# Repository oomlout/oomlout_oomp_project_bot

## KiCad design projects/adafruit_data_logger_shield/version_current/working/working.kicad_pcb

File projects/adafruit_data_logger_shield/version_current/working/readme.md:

# Data-Logger-shield by adafruit  
This is a harvested standardized copy of a project from github.  
The original project can be found at:  
https://github.com/adafruit/Data-Logger-shield  
Please consult that link for additional, details, files, and license information.  
Note: It was auto harvested and if the original repo had more than one board file or anything out of the ordinary the files here are likely not representative.

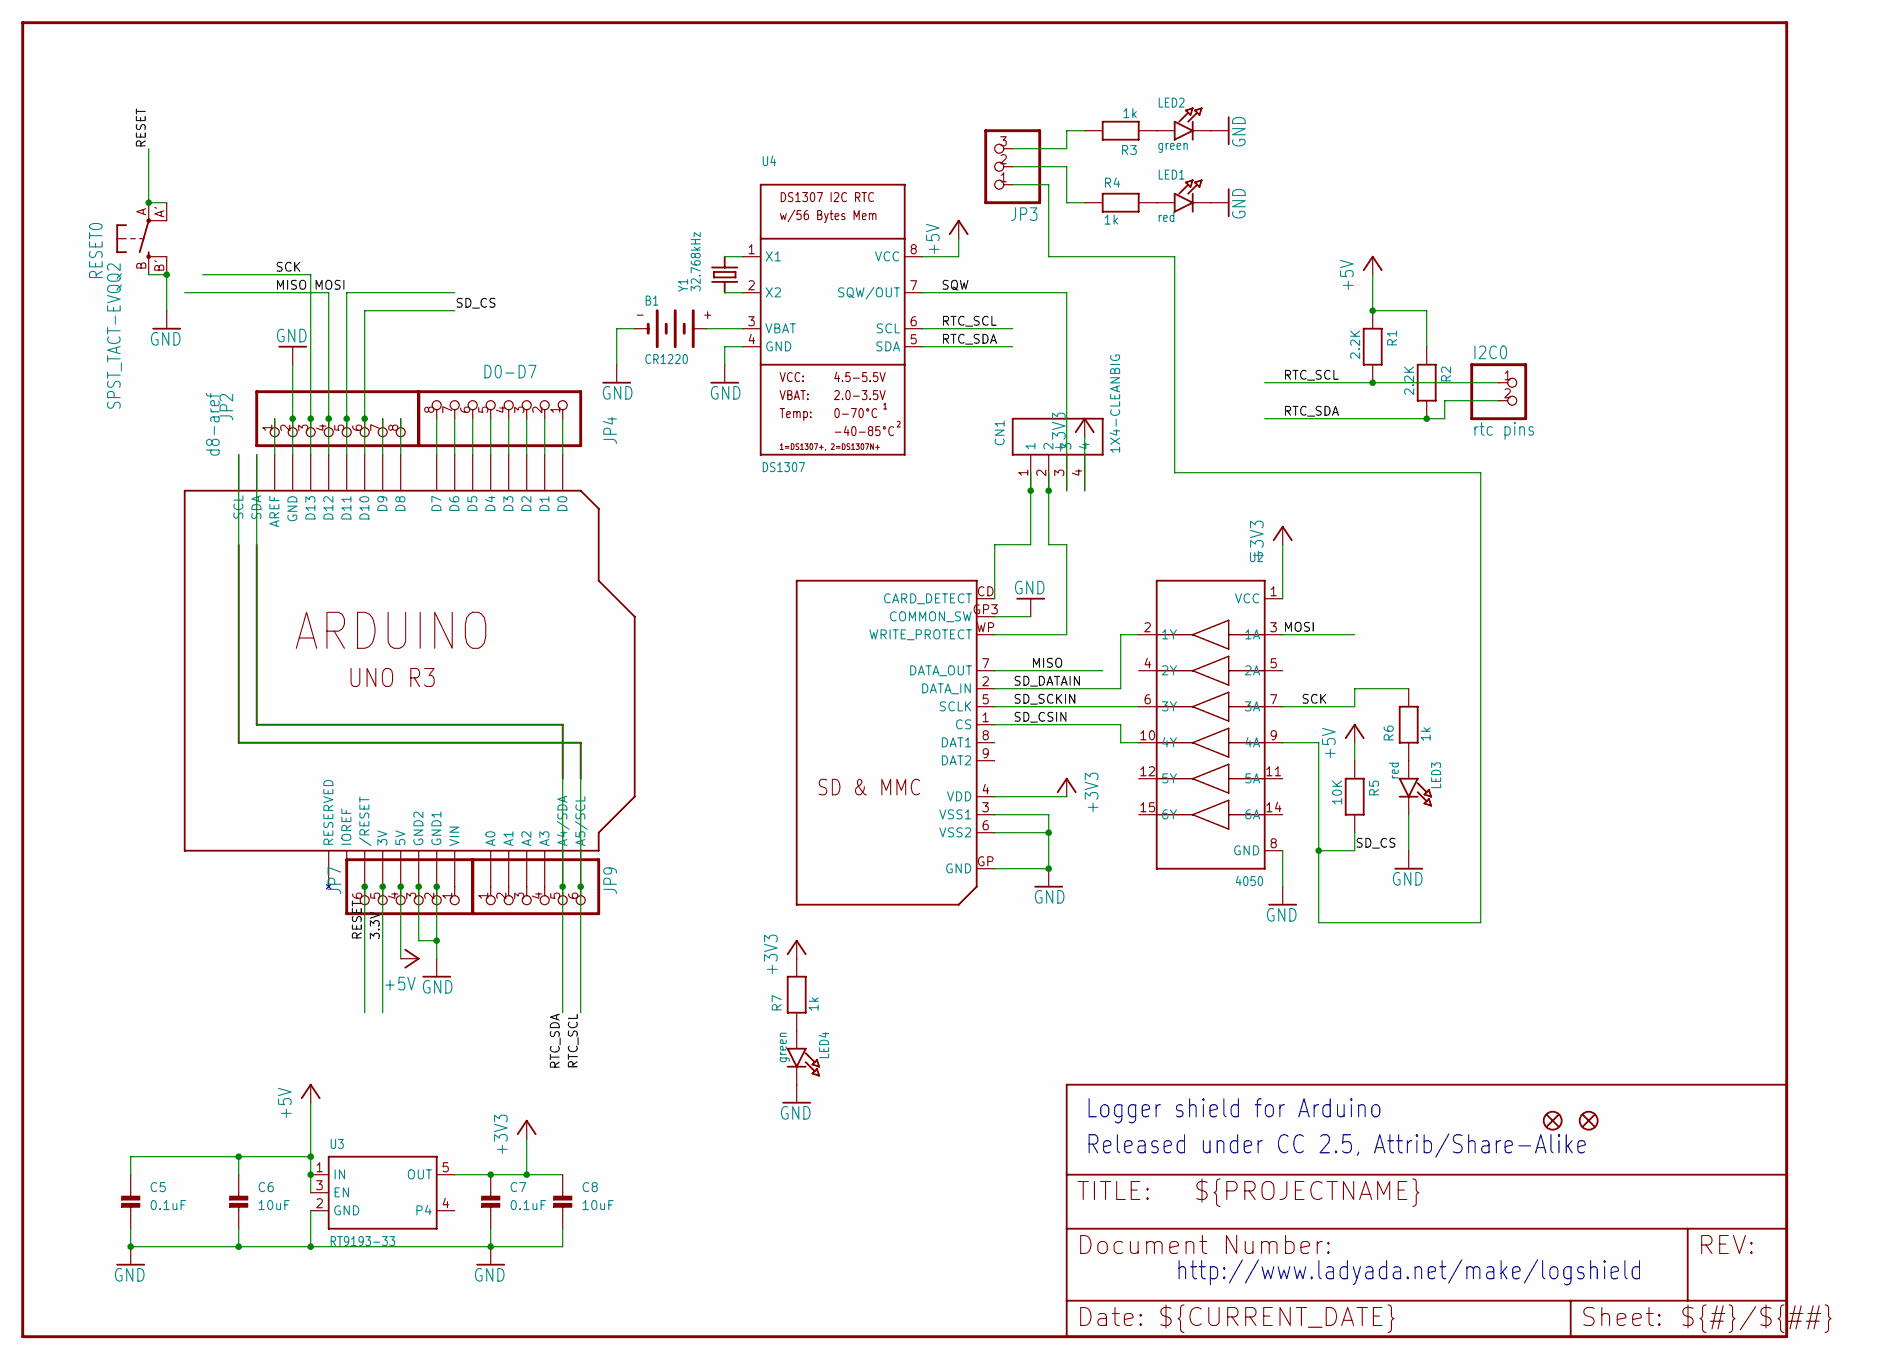
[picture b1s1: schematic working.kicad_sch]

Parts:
B1: CR1220
C5, C7: 0.1uF; 0805
C6, C8: 10uF; 0805
CN1: 1X4-CLEANBIG; 1X04-CLEANBIG
FID1, FID3: FIDUCIAL1X2.5; FIDUCIAL-1X2.5
I2C0: rtc pins; 1X02
JP2: d8-aref; 1X08-BIG
JP3: HEADER-1X3ROUND; 1X03_ROUND
JP4: D0-D7; 1X08-BIG
JP7, JP9: PINHD-1X6B; 1X06-BIG
LED1, LED3: red; CHIPLED_0805
LED2, LED4: green; CHIPLED_0805
R1, R2: 2.2K; 0805
R3, R4, R6, R7: 1k; 0805
R5: 10K; 0805
RESET0: SPST_TACT-EVQQ2; EVQ-Q2
U1: ARDUINOR3-DIMENSION; ARDUINOR3
U2: 4050; SOIC16
U3: RT9193-33; SOT23-5
U4: DS1307; SOIC8_150MIL
U$2: SDMMC06132; 06132
Y1: 32.768kHz; CRYSTAL_8X3.8

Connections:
3.3V: JP7.5, U1.3V
+3V3: C7.1, C8.1, CN1.4, R7.2, U2.1 (VCC), U3.5 (OUT), U$2.4 (VDD)
+5V: C5.1, C6.1, JP7.4, R1.1, R2.1, R5.1, U1.5V, U3.1 (IN), U3.3 (EN), U4.8 (VCC)
GND: B1.-, C5.2, C6.2, C7.2, C8.2, JP2.2, JP7.2, JP7.3, LED1.C, LED2.C, LED3.C, LED4.C, RESET0.B (S), RESET0.B' (S1), U1.GND, U1.GND1, U1.GND2, U2.8 (GND), U3.2 (GND), U4.4 (GND), U$2.3 (VSS1), U$2.6 (VSS2), U$2.GP (GND), U$2.GP3 (COMMON_SW)
MISO: JP2.4, U1.D12, U$2.7 (DATA_OUT)
MOSI: JP2.5, U1.D11, U2.3 (1A)
unnamed: LED1.A, R4.2
unnamed: U4.2 (X2), Y1.P$1 (1)
unnamed: U4.1 (X1), Y1.P$4 (2)
unnamed: LED2.A, R3.1
unnamed: LED3.A, R6.1
unnamed: B1.+$1 (+), U4.3 (VBAT)
unnamed: JP7.1, U1.VIN
unnamed: JP3.3, R3.2
unnamed: JP3.2, R4.1
unnamed: JP4.1, U1.D0
unnamed: JP4.2, U1.D1
unnamed: JP4.3, U1.D2
unnamed: JP4.4, U1.D3
unnamed: JP4.5, U1.D4
unnamed: JP4.6, U1.D5
unnamed: JP4.7, U1.D6
unnamed: JP4.8, U1.D7
unnamed: JP2.1, U1.AREF
unnamed: JP2.7, U1.D9
unnamed: JP2.8, U1.D8
unnamed: LED4.A, R7.1
unnamed: JP9.1, U1.A0
unnamed: JP9.2, U1.A1
unnamed: JP9.3, U1.A2
unnamed: JP9.4, U1.A3
RESET: JP7.6, RESET0.A, RESET0.A' (P1), U1.RESET (/RESET)
RTC_SCL: I2C0.1, JP9.6, R1.2, U1.A5 (A5/SCL), U1.SCL, U4.6 (SCL)
RTC_SDA: I2C0.2, JP9.5, R2.2, U1.A4 (A4/SDA), U1.SDA, U4.5 (SDA)
SCK: JP2.3, R6.2, U1.D13, U2.7 (3A)
SD_CD: CN1.1, U$2.CD (CARD_DETECT)
SD_CS: JP2.6, JP3.1, R5.2, U1.D10, U2.9 (4A)
SD_CSIN: U2.10 (4Y), U$2.1 (CS)
SD_DATAIN: U2.2 (1Y), U$2.2 (DATA_IN)
SD_SCKIN: U2.6 (3Y), U$2.5 (SCLK)
SD_WP: CN1.2, U$2.WP (WRITE_PROTECT)
SQW: CN1.3, U4.7 (SQW/OUT)

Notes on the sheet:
Released under CC 2.5, Attrib/Share-Alike
http://www.ladyada.net/make/logshield
Logger shield for Arduino

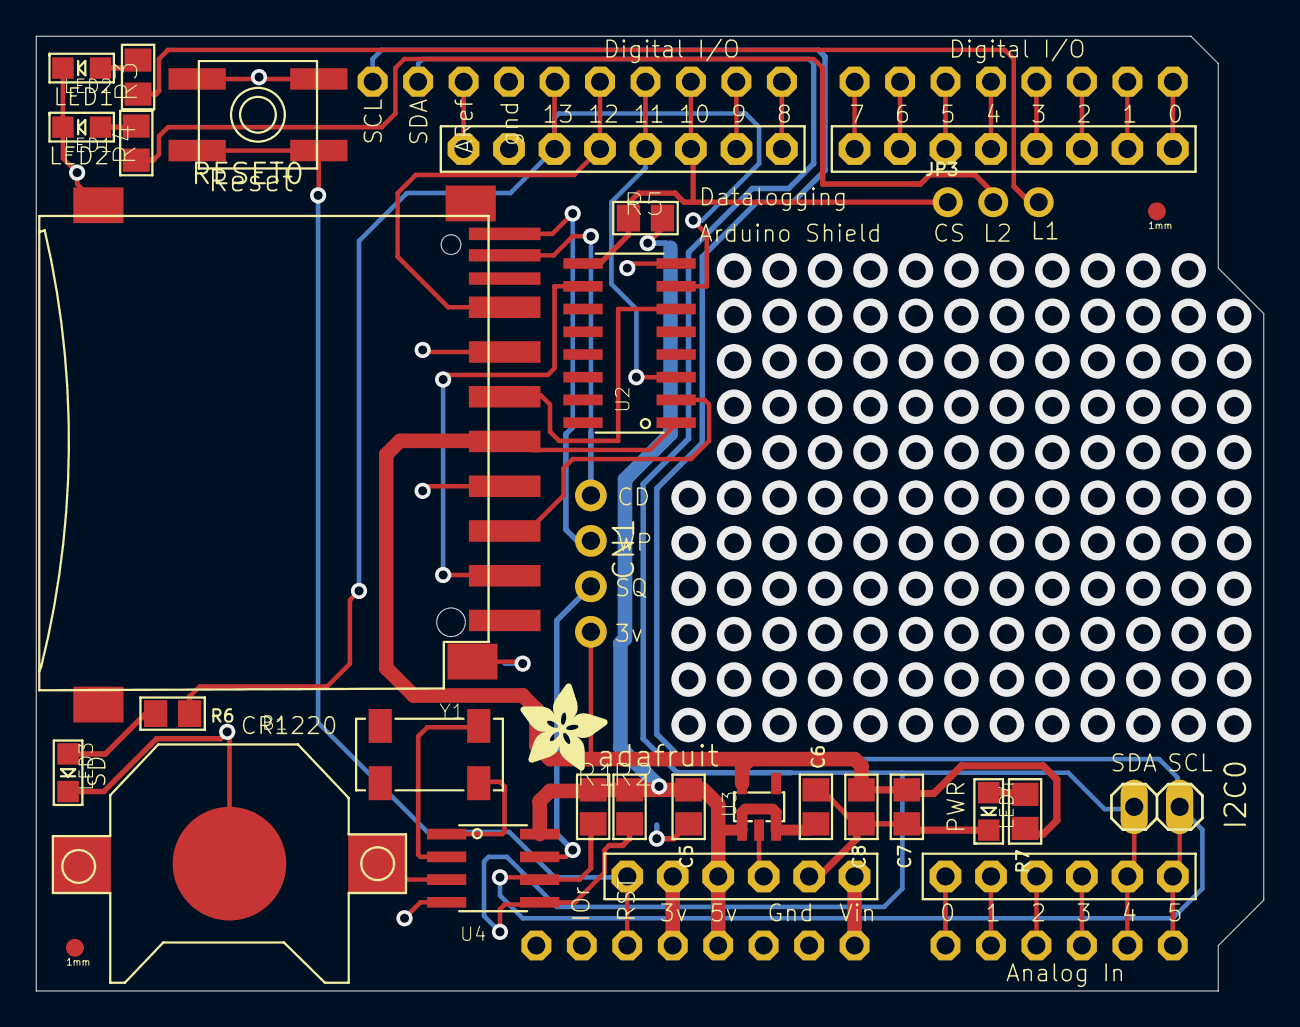
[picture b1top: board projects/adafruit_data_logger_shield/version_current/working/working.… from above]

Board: 2 copper layers, 68.6 x 53.3 mm, 34 parts (1 on the bottom side), 42 nets.

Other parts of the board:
U$1: ADAFRUIT_TEXT_30MM
U$5: ADAFRUIT_5MM

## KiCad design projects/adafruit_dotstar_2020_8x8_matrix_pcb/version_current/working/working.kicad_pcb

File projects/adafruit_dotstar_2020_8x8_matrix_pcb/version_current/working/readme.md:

# DotStar-2020-8x8-Matrix-PCB by adafruit  
This is a harvested standardized copy of a project from github.  
The original project can be found at:  
https://github.com/adafruit/DotStar-2020-8x8-Matrix-PCB  
Please consult that link for additional, details, files, and license information.  
Note: It was auto harvested and if the original repo had more than one board file or anything out of the ordinary the files here are likely not representative.

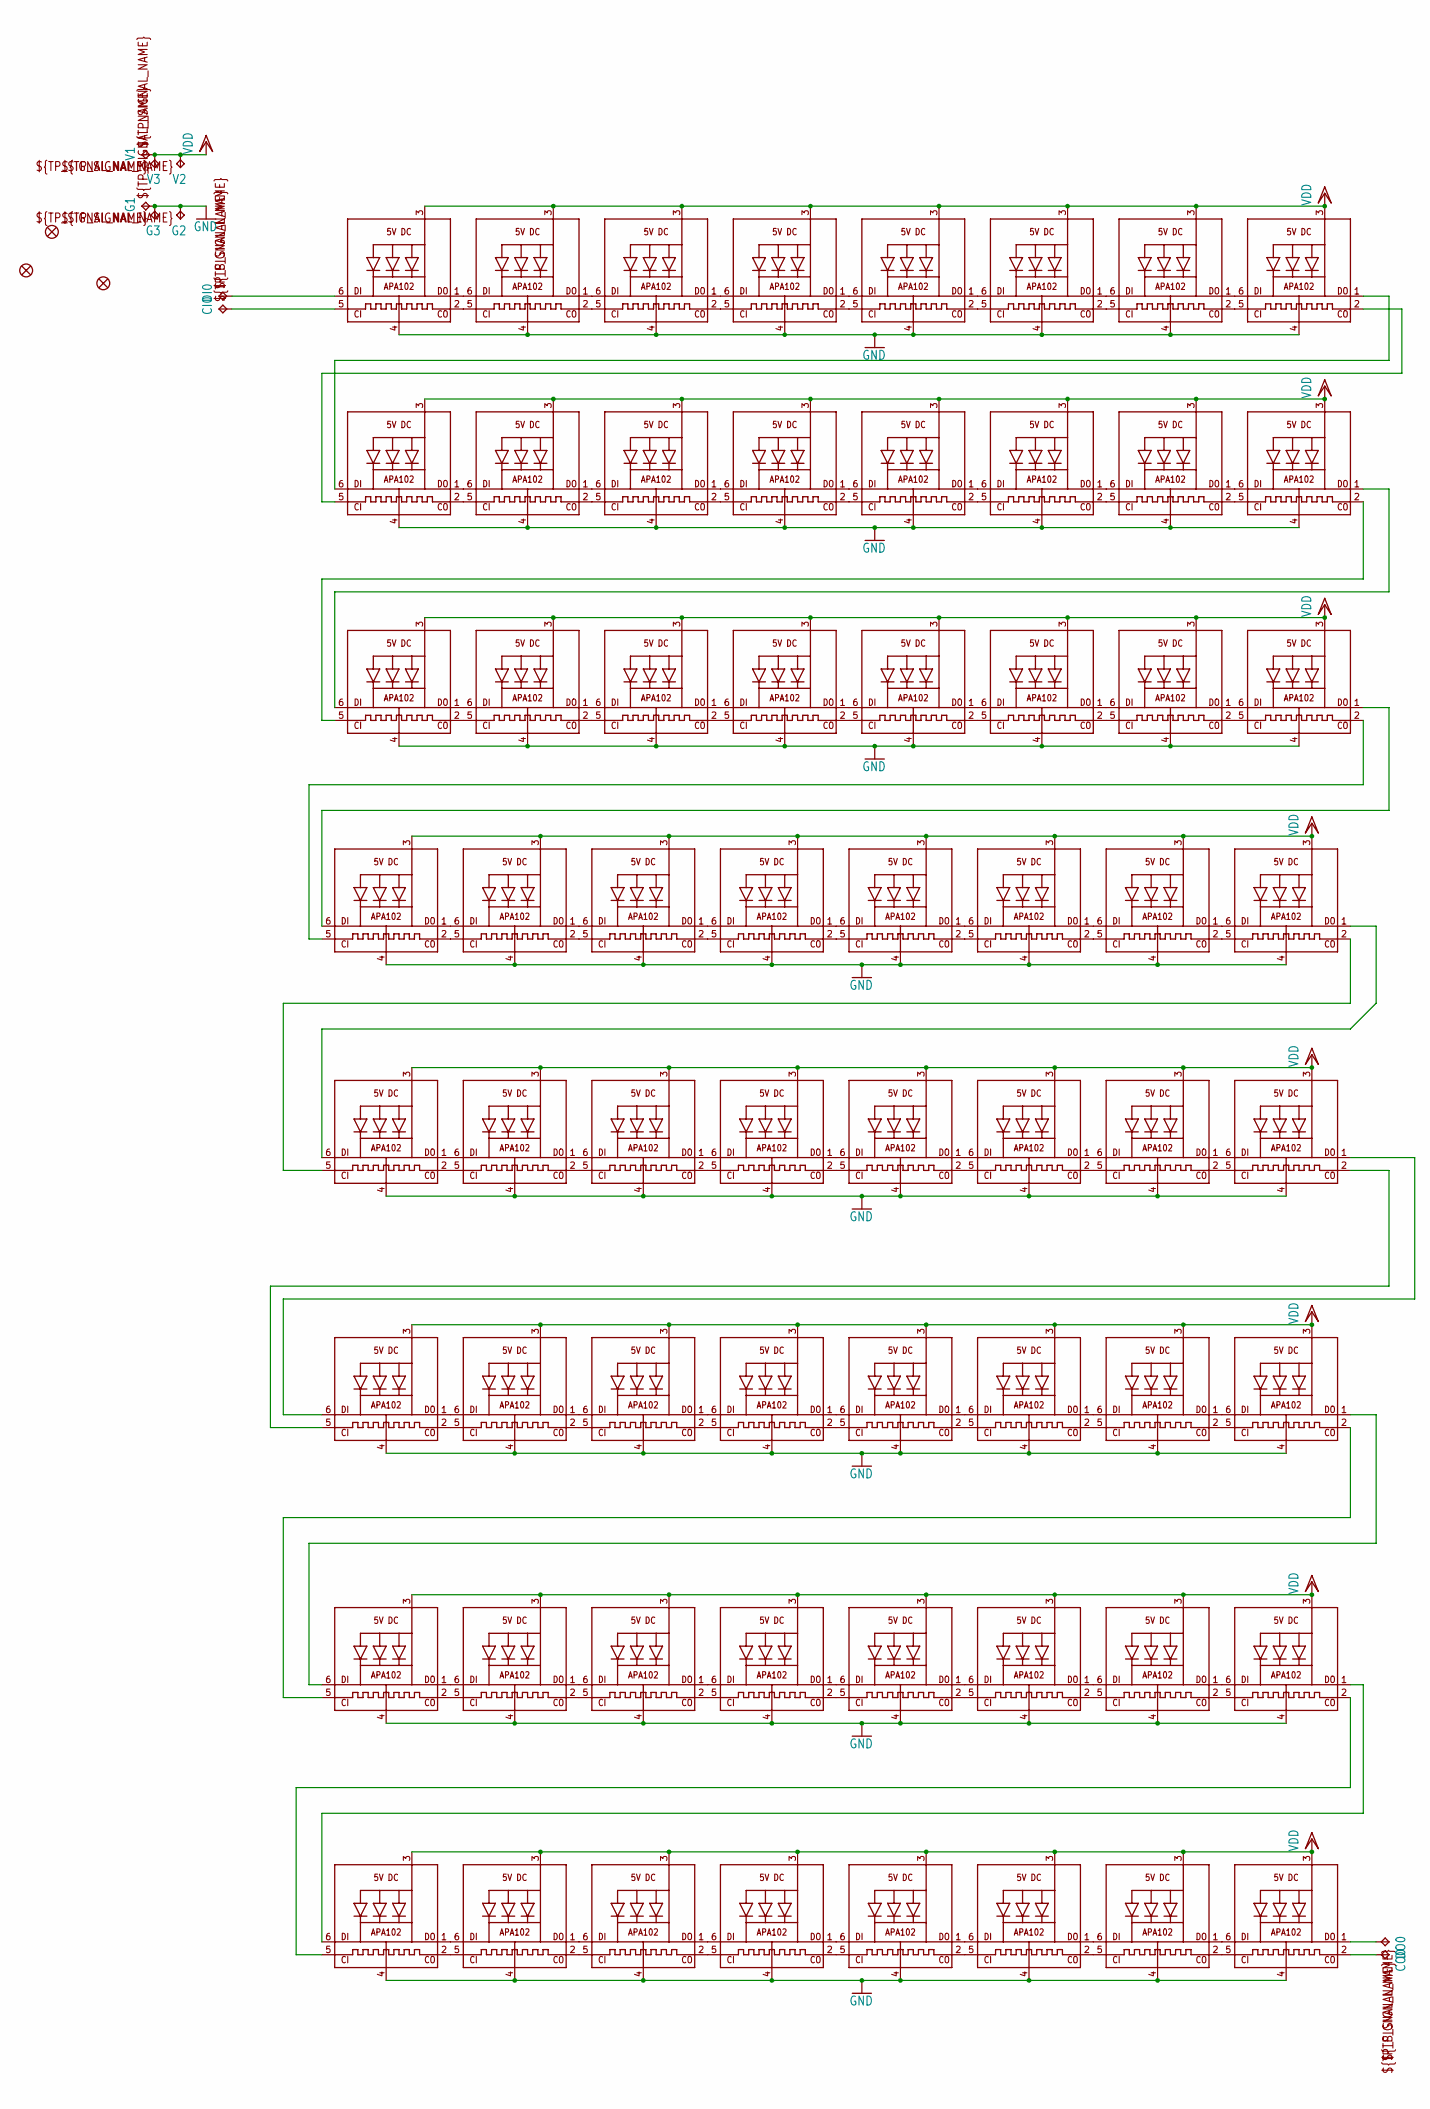
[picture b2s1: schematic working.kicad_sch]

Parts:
CI0: TPTP20R; TP20R
CO0: TPTP20R; TP20R
DI0: TPTP20R; TP20R
DO0: TPTP20R; TP20R
FID1, FID2, FID3: FIDUCIAL_0.5MM
G1, G2, G3: TPTP20R; TP20R
LED1, LED2, LED3, LED4, LED5, LED6, LED7, LED8, LED9, LED10, LED11, LED12, LED13, LED14, LED15, LED16, LED17, LED18, LED19, LED20, LED21, LED22, LED23, LED24, LED25, LED26, LED27, LED28, LED29, LED30, LED31, LED32, LED33, LED34, LED35, LED36, LED37, LED38, LED39, LED40, LED41, LED42, LED43, LED44, LED45, LED46, LED47, LED48, LED49, LED50, LED51, LED52, LED53, LED54, LED55, LED56, LED57, LED58, LED59, LED60, LED61, LED62, LED63, LED64: APA1022020; APA102_2020
V1, V2, V3: TPTP20R; TP20R

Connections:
C0: CO0.TP, LED64.2 (CKO)
CIN: CI0.TP, LED1.5 (CKI)
D0: DO0.TP, LED64.1 (DO)
DIN: DI0.TP, LED1.6 (DI)
GND: G1.TP, G2.TP, G3.TP, LED1.4 (GND), LED2.4 (GND), LED3.4 (GND), LED4.4 (GND), LED5.4 (GND), LED6.4 (GND), LED7.4 (GND), LED8.4 (GND), LED9.4 (GND), LED10.4 (GND), LED11.4 (GND), LED12.4 (GND), LED13.4 (GND), LED14.4 (GND), LED15.4 (GND), LED16.4 (GND), LED17.4 (GND), LED18.4 (GND), LED19.4 (GND), LED20.4 (GND), LED21.4 (GND), LED22.4 (GND), LED23.4 (GND), LED24.4 (GND), LED25.4 (GND), LED26.4 (GND), LED27.4 (GND), LED28.4 (GND), LED29.4 (GND), LED30.4 (GND), LED31.4 (GND), LED32.4 (GND), LED33.4 (GND), LED34.4 (GND), LED35.4 (GND), LED36.4 (GND), LED37.4 (GND), LED38.4 (GND), LED39.4 (GND), LED40.4 (GND), LED41.4 (GND), LED42.4 (GND), LED43.4 (GND), LED44.4 (GND), LED45.4 (GND), LED46.4 (GND), LED47.4 (GND), LED48.4 (GND), LED49.4 (GND), LED50.4 (GND), LED51.4 (GND), LED52.4 (GND), LED53.4 (GND), LED54.4 (GND), LED55.4 (GND), LED56.4 (GND), LED57.4 (GND), LED58.4 (GND), LED59.4 (GND), LED60.4 (GND), LED61.4 (GND), LED62.4 (GND), LED63.4 (GND), LED64.4 (GND)
unnamed: LED1.1 (DO), LED2.6 (DI)
unnamed: LED1.2 (CKO), LED2.5 (CKI)
unnamed: LED2.1 (DO), LED3.6 (DI)
unnamed: LED2.2 (CKO), LED3.5 (CKI)
unnamed: LED3.1 (DO), LED4.6 (DI)
unnamed: LED3.2 (CKO), LED4.5 (CKI)
unnamed: LED4.1 (DO), LED5.6 (DI)
unnamed: LED4.2 (CKO), LED5.5 (CKI)
unnamed: LED5.1 (DO), LED6.6 (DI)
unnamed: LED5.2 (CKO), LED6.5 (CKI)
unnamed: LED6.1 (DO), LED7.6 (DI)
unnamed: LED6.2 (CKO), LED7.5 (CKI)
unnamed: LED7.1 (DO), LED8.6 (DI)
unnamed: LED7.2 (CKO), LED8.5 (CKI)
unnamed: LED9.1 (DO), LED10.6 (DI)
unnamed: LED9.2 (CKO), LED10.5 (CKI)
unnamed: LED10.1 (DO), LED11.6 (DI)
unnamed: LED10.2 (CKO), LED11.5 (CKI)
unnamed: LED11.1 (DO), LED12.6 (DI)
unnamed: LED11.2 (CKO), LED12.5 (CKI)
unnamed: LED12.1 (DO), LED13.6 (DI)
unnamed: LED12.2 (CKO), LED13.5 (CKI)
unnamed: LED13.1 (DO), LED14.6 (DI)
unnamed: LED13.2 (CKO), LED14.5 (CKI)
unnamed: LED14.1 (DO), LED15.6 (DI)
unnamed: LED14.2 (CKO), LED15.5 (CKI)
unnamed: LED15.1 (DO), LED16.6 (DI)
unnamed: LED15.2 (CKO), LED16.5 (CKI)
unnamed: LED17.1 (DO), LED18.6 (DI)
unnamed: LED17.2 (CKO), LED18.5 (CKI)
unnamed: LED18.1 (DO), LED19.6 (DI)
unnamed: LED18.2 (CKO), LED19.5 (CKI)
unnamed: LED19.1 (DO), LED20.6 (DI)
unnamed: LED19.2 (CKO), LED20.5 (CKI)
unnamed: LED20.1 (DO), LED21.6 (DI)
unnamed: LED20.2 (CKO), LED21.5 (CKI)
unnamed: LED21.1 (DO), LED22.6 (DI)
unnamed: LED21.2 (CKO), LED22.5 (CKI)
unnamed: LED22.1 (DO), LED23.6 (DI)
unnamed: LED22.2 (CKO), LED23.5 (CKI)
unnamed: LED23.1 (DO), LED24.6 (DI)
unnamed: LED23.2 (CKO), LED24.5 (CKI)
unnamed: LED25.1 (DO), LED26.6 (DI)
unnamed: LED25.2 (CKO), LED26.5 (CKI)
unnamed: LED26.1 (DO), LED27.6 (DI)
unnamed: LED26.2 (CKO), LED27.5 (CKI)
unnamed: LED27.1 (DO), LED28.6 (DI)
unnamed: LED27.2 (CKO), LED28.5 (CKI)
unnamed: LED28.1 (DO), LED29.6 (DI)
unnamed: LED28.2 (CKO), LED29.5 (CKI)
unnamed: LED29.1 (DO), LED30.6 (DI)
unnamed: LED29.2 (CKO), LED30.5 (CKI)
unnamed: LED30.1 (DO), LED31.6 (DI)
unnamed: LED30.2 (CKO), LED31.5 (CKI)
unnamed: LED31.1 (DO), LED32.6 (DI)
unnamed: LED31.2 (CKO), LED32.5 (CKI)
unnamed: LED33.1 (DO), LED34.6 (DI)
unnamed: LED33.2 (CKO), LED34.5 (CKI)
unnamed: LED34.1 (DO), LED35.6 (DI)
unnamed: LED34.2 (CKO), LED35.5 (CKI)
unnamed: LED35.1 (DO), LED36.6 (DI)
unnamed: LED35.2 (CKO), LED36.5 (CKI)
unnamed: LED36.1 (DO), LED37.6 (DI)
unnamed: LED36.2 (CKO), LED37.5 (CKI)
unnamed: LED37.1 (DO), LED38.6 (DI)
unnamed: LED37.2 (CKO), LED38.5 (CKI)
unnamed: LED38.1 (DO), LED39.6 (DI)
unnamed: LED38.2 (CKO), LED39.5 (CKI)
unnamed: LED39.1 (DO), LED40.6 (DI)
unnamed: LED39.2 (CKO), LED40.5 (CKI)
unnamed: LED41.1 (DO), LED42.6 (DI)
unnamed: LED41.2 (CKO), LED42.5 (CKI)
unnamed: LED42.1 (DO), LED43.6 (DI)
unnamed: LED42.2 (CKO), LED43.5 (CKI)
unnamed: LED43.1 (DO), LED44.6 (DI)
unnamed: LED43.2 (CKO), LED44.5 (CKI)
unnamed: LED44.1 (DO), LED45.6 (DI)
unnamed: LED44.2 (CKO), LED45.5 (CKI)
unnamed: LED45.1 (DO), LED46.6 (DI)
unnamed: LED45.2 (CKO), LED46.5 (CKI)
unnamed: LED46.1 (DO), LED47.6 (DI)
unnamed: LED46.2 (CKO), LED47.5 (CKI)
unnamed: LED47.1 (DO), LED48.6 (DI)
unnamed: LED47.2 (CKO), LED48.5 (CKI)
unnamed: LED49.1 (DO), LED50.6 (DI)
unnamed: LED49.2 (CKO), LED50.5 (CKI)
unnamed: LED50.1 (DO), LED51.6 (DI)
unnamed: LED50.2 (CKO), LED51.5 (CKI)
unnamed: LED51.1 (DO), LED52.6 (DI)
unnamed: LED51.2 (CKO), LED52.5 (CKI)
unnamed: LED52.1 (DO), LED53.6 (DI)
unnamed: LED52.2 (CKO), LED53.5 (CKI)
unnamed: LED53.1 (DO), LED54.6 (DI)
unnamed: LED53.2 (CKO), LED54.5 (CKI)
unnamed: LED54.1 (DO), LED55.6 (DI)
unnamed: LED54.2 (CKO), LED55.5 (CKI)
unnamed: LED55.1 (DO), LED56.6 (DI)
unnamed: LED55.2 (CKO), LED56.5 (CKI)
unnamed: LED57.1 (DO), LED58.6 (DI)
unnamed: LED57.2 (CKO), LED58.5 (CKI)
unnamed: LED58.1 (DO), LED59.6 (DI)
unnamed: LED58.2 (CKO), LED59.5 (CKI)
unnamed: LED59.1 (DO), LED60.6 (DI)
unnamed: LED59.2 (CKO), LED60.5 (CKI)
unnamed: LED60.1 (DO), LED61.6 (DI)
unnamed: LED60.2 (CKO), LED61.5 (CKI)
unnamed: LED61.1 (DO), LED62.6 (DI)
unnamed: LED61.2 (CKO), LED62.5 (CKI)
unnamed: LED62.1 (DO), LED63.6 (DI)
unnamed: LED62.2 (CKO), LED63.5 (CKI)
unnamed: LED63.1 (DO), LED64.6 (DI)
unnamed: LED63.2 (CKO), LED64.5 (CKI)
unnamed: LED8.1 (DO), LED9.6 (DI)
unnamed: LED8.2 (CKO), LED9.5 (CKI)
unnamed: LED16.1 (DO), LED17.6 (DI)
unnamed: LED16.2 (CKO), LED17.5 (CKI)
unnamed: LED24.1 (DO), LED25.6 (DI)
unnamed: LED24.2 (CKO), LED25.5 (CKI)
unnamed: LED32.1 (DO), LED33.6 (DI)
unnamed: LED32.2 (CKO), LED33.5 (CKI)
unnamed: LED56.1 (DO), LED57.6 (DI)
unnamed: LED56.2 (CKO), LED57.5 (CKI)
unnamed: LED48.2 (CKO), LED49.5 (CKI)
unnamed: LED48.1 (DO), LED49.6 (DI)
unnamed: LED40.2 (CKO), LED41.5 (CKI)
unnamed: LED40.1 (DO), LED41.6 (DI)
VDD: LED1.3 (VDD), LED2.3 (VDD), LED3.3 (VDD), LED4.3 (VDD), LED5.3 (VDD), LED6.3 (VDD), LED7.3 (VDD), LED8.3 (VDD), LED9.3 (VDD), LED10.3 (VDD), LED11.3 (VDD), LED12.3 (VDD), LED13.3 (VDD), LED14.3 (VDD), LED15.3 (VDD), LED16.3 (VDD), LED17.3 (VDD), LED18.3 (VDD), LED19.3 (VDD), LED20.3 (VDD), LED21.3 (VDD), LED22.3 (VDD), LED23.3 (VDD), LED24.3 (VDD), LED25.3 (VDD), LED26.3 (VDD), LED27.3 (VDD), LED28.3 (VDD), LED29.3 (VDD), LED30.3 (VDD), LED31.3 (VDD), LED32.3 (VDD), LED33.3 (VDD), LED34.3 (VDD), LED35.3 (VDD), LED36.3 (VDD), LED37.3 (VDD), LED38.3 (VDD), LED39.3 (VDD), LED40.3 (VDD), LED41.3 (VDD), LED42.3 (VDD), LED43.3 (VDD), LED44.3 (VDD), LED45.3 (VDD), LED46.3 (VDD), LED47.3 (VDD), LED48.3 (VDD), LED49.3 (VDD), LED50.3 (VDD), LED51.3 (VDD), LED52.3 (VDD), LED53.3 (VDD), LED54.3 (VDD), LED55.3 (VDD), LED56.3 (VDD), LED57.3 (VDD), LED58.3 (VDD), LED59.3 (VDD), LED60.3 (VDD), LED61.3 (VDD), LED62.3 (VDD), LED63.3 (VDD), LED64.3 (VDD), V1.TP, V2.TP, V3.TP

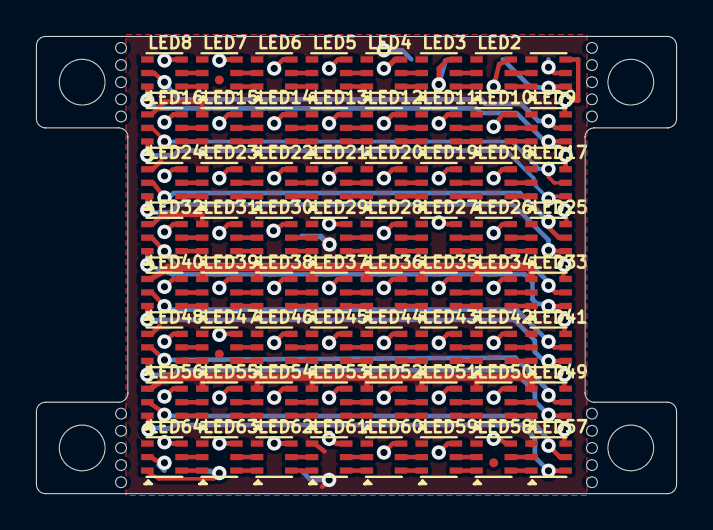
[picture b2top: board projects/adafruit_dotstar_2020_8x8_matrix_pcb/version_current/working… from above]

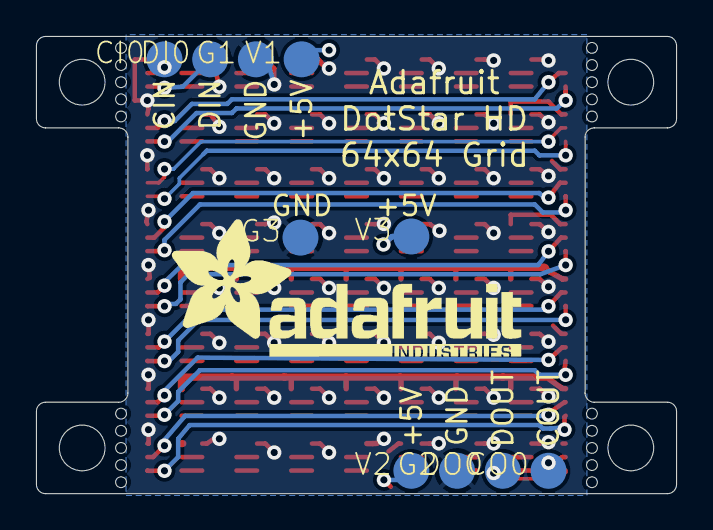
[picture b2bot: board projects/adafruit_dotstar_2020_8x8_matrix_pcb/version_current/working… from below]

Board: 2 copper layers, 35.6 x 25.4 mm, 102 parts (11 on the bottom side), 132 nets.

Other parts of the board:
@HOLE0, @HOLE1, @HOLE2, @HOLE3, @HOLE4, @HOLE5, @HOLE6, @HOLE7, @HOLE8, @HOLE9, @HOLE10, @HOLE11, @HOLE12, @HOLE13, @HOLE14, @HOLE15, @HOLE16, @HOLE17, @HOLE18, @HOLE19, @HOLE20, @HOLE21, @HOLE22, @HOLE23: (no value)
U$1: ADAFRUIT_TEXT_20MM

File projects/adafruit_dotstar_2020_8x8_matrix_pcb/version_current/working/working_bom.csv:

Row,Description,Part,References,Value,Footprint,Quantity Per PCB,Status,Datasheet
1,,TPTP20R,CI0 CO0 DI0 DO0 G1 G2 G3 V1 V2 V3,TPTP20R,TP20R,10, ,
2,,APA1022020,LED1 LED2 LED3 LED4 LED5 LED6 LED7 LED8 LED9 LED10 LED11 LED12 LED13 LED14 LED15 LED16 LED17 LED18 LED19 LED20 LED21 LED22 LED23 LED24 LED25 LED26 LED27 LED28 LED29 LED30 LED31 LED32 LED33 LED34 LED35 LED36 LED37 LED38 LED39 LED40 LED41 LED42 LED43 LED44 LED45 LED46 LED47 LED48 LED49 LED50 LED51 LED52 LED53 LED54 LED55 LED56 LED57 LED58 LED59 LED60 LED61 LED62 LED63 LED64,APA1022020,APA102_2020,64, ,





Project info:
Schematic:,working
Variant:,default
Revision:,
Date:,2023-08-03_17-21-23
KiCad Version:,7.0.6-7.0.6~ubuntu22.04.1
Statistics:
Component Groups:,2
Component Count:,74 (0 SMD/ 0 THT)
Fitted Components:,74 (0 SMD/ 0 THT)
Number of PCBs:,1
Total Components:,74

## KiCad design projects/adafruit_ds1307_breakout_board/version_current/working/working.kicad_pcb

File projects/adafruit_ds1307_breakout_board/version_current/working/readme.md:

# OOMP Project  
## DS1307-breakout-board  by adafruit  
  
oomp key: oomp_projects_flat_adafruit_ds1307_breakout_board  
(snippet of original readme)  
  
-- Adafruit DS1307 Real Time Clock Assembled Breakout Board PCB  
  
<a href="http://www.adafruit.com/products/3296"><br/>  
Click here to purchase one from the Adafruit shop</a>  
  
PCB files for the Adafruit DS1307 Real Time Clock Assembled Breakout Board. Format is EagleCAD schematic and board layout  
* https://www.adafruit.com/product/3296  
  
--- Description  
  
This is a great battery-backed real time clock (RTC) that allows your microcontroller project to keep track of time even if it is reprogrammed, or if the power is lost. Perfect for datalogging, clock-building, time stamping, timers and alarms, etc. The DS1307 is the most popular RTC - but it requires 5V power to work (although we've used it with 5V power and 3.3V logic successfully)  
  
Works great with an [Arduino using our RTC library](https://github.com/adafruit/RTClib) or with a [Raspberry Pi (or similar single board linux computer)](https://learn.adafruit.com/adding-a-real-time-clock-to-raspberry-pi)  
  
The DS1307 is simple and inexpensive but not a high precision device. It may lose or gain up to 2 seconds a day. For a high-precision, temperature compensated alternative, [please check out the DS3231 precision RTC](https://www.adafruit.com/products/3013). If you do not need a DS1307, or you need a 3.3V-power/logic capable RTC please check out our affordable [PCF8523 RTC breakout](http://www.adafruit.com/products/3295)  
  
--- License  
  
Adafruit invests time and resources providing th  
  full source readme at [readme_src.md](readme_src.md)  
  
source repo at: [https://github.com/adafruit/DS1307-breakout-board](https://github.com/adafruit/DS1307-breakout-board)  
## Board  

## Schematic  

[schematic pdf](working_schematic.pdf)  
## Images

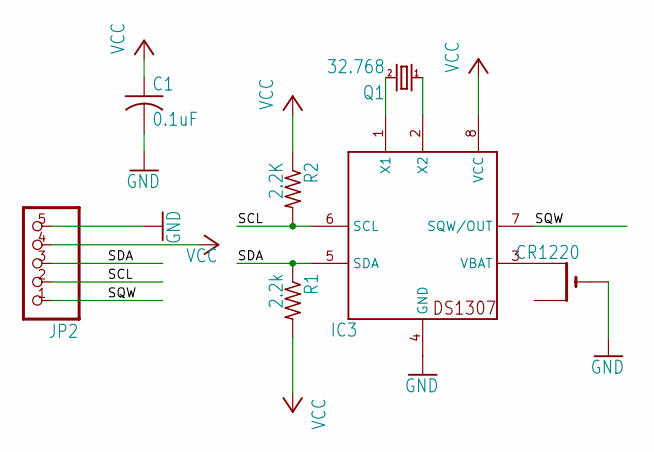
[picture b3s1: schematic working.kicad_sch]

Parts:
BAT0: CR1220; CR1220-THM
C1: 0.1uF; C025-025X050
IC3: DS1307; DIL08
JP2: PINHD-1X5; 1X05
Q1: 32.768; TC38H
R1: 2.2k; 0207_10
R2: 2.2K; 0207_10

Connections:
GND: BAT0.-, C1.2, IC3.4 (GND), JP2.5
unnamed: IC3.1 (X1), Q1.2
unnamed: IC3.2 (X2), Q1.1
unnamed: BAT0.+2 (+1), IC3.3 (VBAT)
SCL: IC3.6 (SCL), JP2.2, R2.2
SDA: IC3.5 (SDA), JP2.3, R1.1
SQW: IC3.7 (SQW/OUT), JP2.1
VCC: C1.1, IC3.8 (VCC), JP2.4, R1.2, R2.1

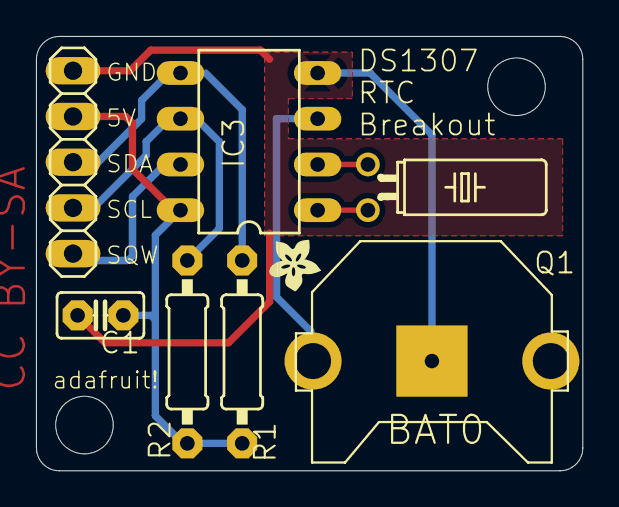
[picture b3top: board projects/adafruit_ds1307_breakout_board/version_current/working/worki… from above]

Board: 16 copper layers, 30.4 x 24.1 mm, 10 parts (0 on the bottom side), 8 nets.

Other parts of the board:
@HOLE0, @HOLE1: (no value)
U$1: ADAFRUIT200MIL

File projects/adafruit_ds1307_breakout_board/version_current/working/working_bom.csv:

Row,Description,Part,References,Value,Footprint,Quantity Per PCB,Status,Datasheet
1,,CR1220THM,BAT0,CR1220,CR1220-THM,1, ,
2,,C-US025-025X050,C1,0.1uF,C025-025X050,1, ,
3,,DS1307,IC3,DS1307,DIL08,1, ,
4,,PINHD-1X5,JP2,PINHD-1X5,1X05,1, ,
5,,CRYTALTC38H,Q1,32.768,TC38H,1, ,
6,,R-US_0207/10,R1 R2,2.2k,0207_10,2, ,





Project info:
Schematic:,working
Variant:,default
Revision:,
Date:,2023-08-03_17-21-23
KiCad Version:,7.0.6-7.0.6~ubuntu22.04.1
Statistics:
Component Groups:,6
Component Count:,7 (0 SMD/ 0 THT)
Fitted Components:,7 (0 SMD/ 0 THT)
Number of PCBs:,1
Total Components:,7

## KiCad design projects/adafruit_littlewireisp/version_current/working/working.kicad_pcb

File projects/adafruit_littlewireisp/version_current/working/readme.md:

# LittleWireISP by adafruit  
This is a harvested standardized copy of a project from github.  
The original project can be found at:  
https://github.com/adafruit/LittleWireISP  
Please consult that link for additional, details, files, and license information.  
Note: It was auto harvested and if the original repo had more than one board file or anything out of the ordinary the files here are likely not representative.

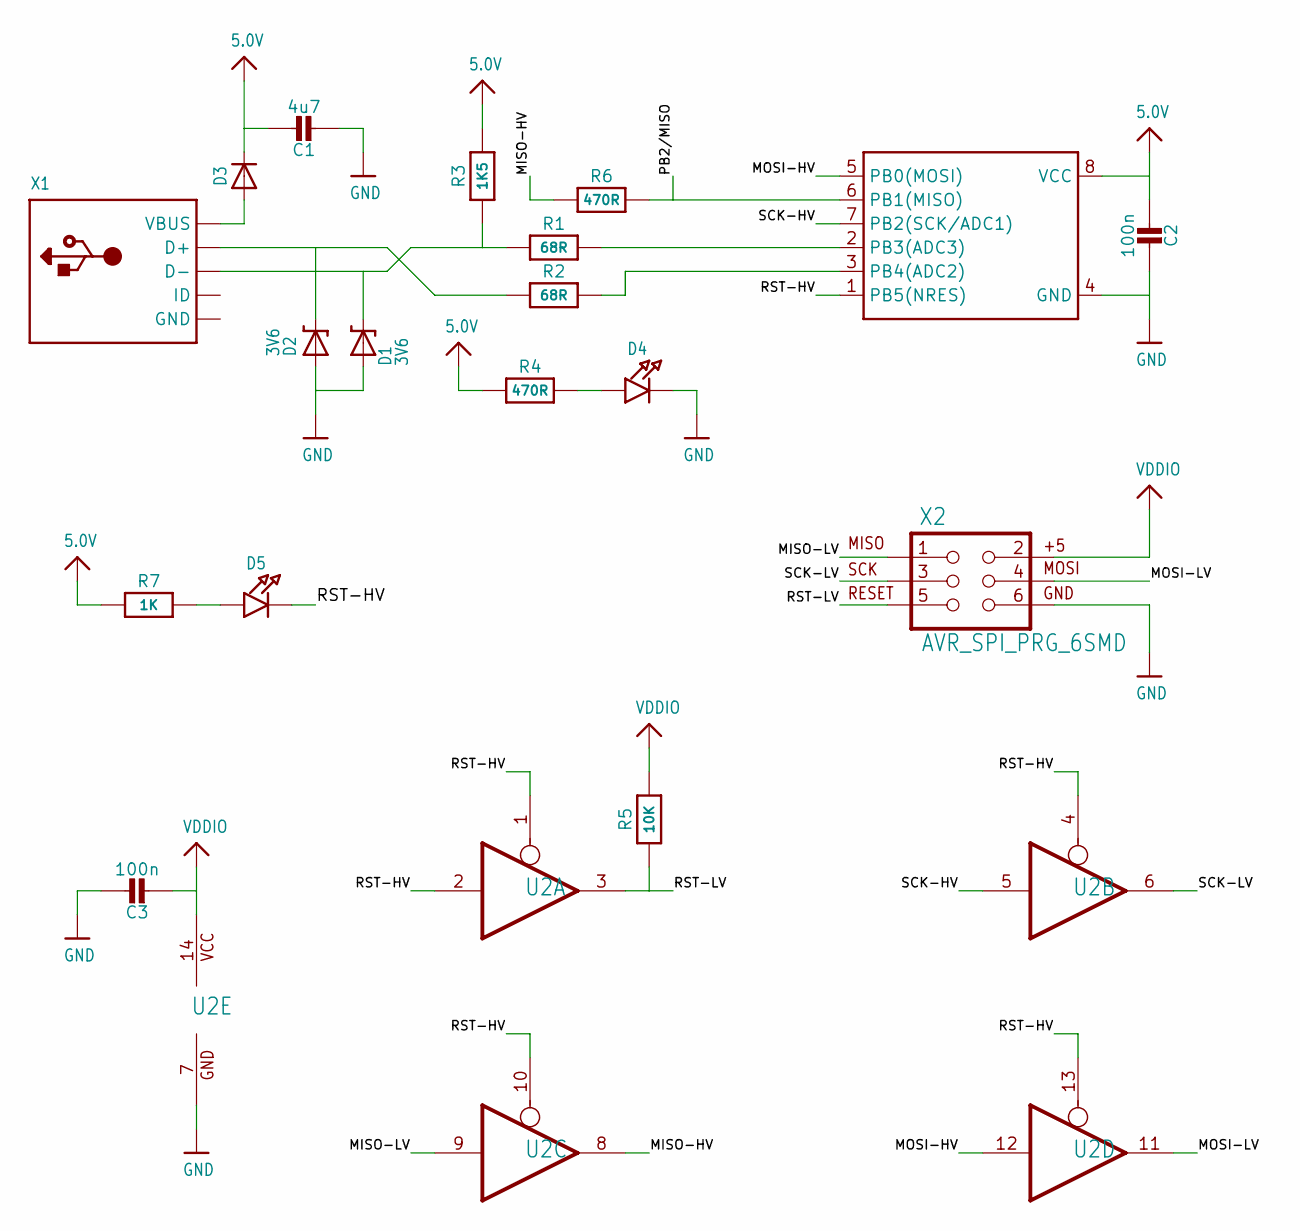
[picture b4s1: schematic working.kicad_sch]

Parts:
C1: 4u7; 0805-NO
C2, C3: 100n; 0805-NO
D1, D2: 3V6; SOD-323
D3: DIODESOD-123; SOD-123
D4, D5: LED0805_NOOUTLINE; CHIPLED_0805_NOOUTLINE
R1, R2: 68R; 0603-NO
R3: 1K5; 0603-NO
R4, R6: 470R; 0603-NO
R5: 10K; 0603-NO
R7: 1K; 0603-NO
U1: ATTINY45; SO08-EIAJ
U2: 74125-SOIC14; SOIC14
X1: USBMINIBLARGE; USB-MINIB_LARGER
X2: AVR_SPI_PRG_6SMD; 2X3_SMD

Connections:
5.0V: C1.1, C2.2, D3.C, R3.2, R4.1, R7.1, U1.8 (VCC)
MISO-HV: R6.1, U2.8 (O)
MISO-LV: U2.9 (I), X2.1
MOSI-HV: U1.5 (PB0(MOSI)), U2.12 (I)
MOSI-LV: U2.11 (O), X2.4
unnamed: D1.C, R1.1, R3.1, X1.D-
unnamed: D2.C, R2.1, X1.D+
unnamed: D5.A, R7.2
unnamed: R1.2, U1.2 (PB3(ADC3))
unnamed: R2.2, U1.3 (PB4(ADC2))
unnamed: D3.A, X1.VBUS
unnamed: D4.A, R4.2
PB2/MISO: R6.2, U1.6 (PB1(MISO))
RST-HV: D5.C, U1.1 (PB5(NRES)), U2.1 (OE), U2.2 (I), U2.4 (OE), U2.10 (OE), U2.13 (OE)
RST-LV: R5.1, U2.3 (O), X2.5
SCK-HV: U1.7 (PB2(SCK/ADC1)), U2.5 (I)
SCK-LV: U2.6 (O), X2.3
VDDIO: C3.2, R5.2, U2.14 (VCC), X2.2

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
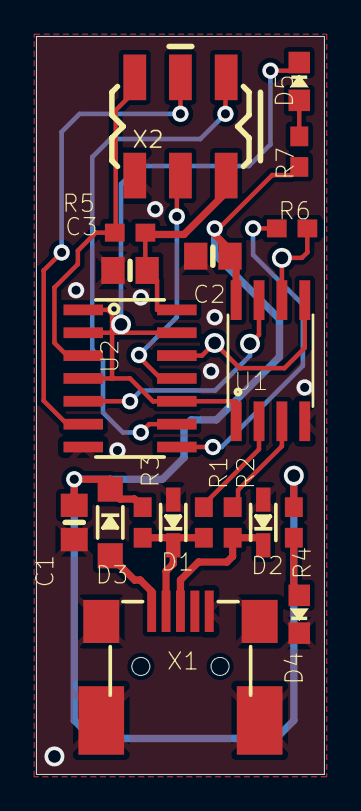
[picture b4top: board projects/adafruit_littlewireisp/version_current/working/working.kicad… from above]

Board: 2 copper layers, 16.0 x 41.0 mm, 19 parts (0 on the bottom side), 19 nets.

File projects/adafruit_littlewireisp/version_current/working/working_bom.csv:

Row,Description,Part,References,Value,Footprint,Quantity Per PCB,Status,Datasheet
1,,CAP_CERAMIC0805-NOOUTLINE,C2 C3,100n,0805-NO,2, ,
2,,CAP_CERAMIC0805-NOOUTLINE,C1,4u7,0805-NO,1, ,
3,,DIODE-ZENERSOD323,D1 D2,3V6,SOD-323,2, ,
4,,DIODESOD-123,D3,DIODESOD-123,SOD-123,1, ,
5,,LED0805_NOOUTLINE,D4 D5,LED0805_NOOUTLINE,CHIPLED_0805_NOOUTLINE,2, ,
6,,RESISTOR_0603_NOOUT,R1 R2,68R,0603-NO,2, ,
7,,RESISTOR_0603_NOOUT,R4 R6,470R,0603-NO,2, ,
8,,RESISTOR_0603_NOOUT,R7,1K,0603-NO,1, ,
9,,RESISTOR_0603_NOOUT,R3,1K5,0603-NO,1, ,
10,,RESISTOR_0603_NOOUT,R5,10K,0603-NO,1, ,
11,,74125-SOIC14,U2,74125-SOIC14,SOIC14,1, ,
12,,ATTINY45,U1,ATTINY45,SO08-EIAJ,1, ,
13,,AVR_SPI_PRG_6SMD,X2,AVR_SPI_PRG_6SMD,2X3_SMD,1, ,
14,,USBMINIBLARGE,X1,USBMINIBLARGE,USB-MINIB_LARGER,1, ,





Project info:
Schematic:,working
Variant:,default
Revision:,
Date:,2023-08-03_17-21-23
KiCad Version:,7.0.6-7.0.6~ubuntu22.04.1
Statistics:
Component Groups:,14
Component Count:,19 (0 SMD/ 0 THT)
Fitted Components:,19 (0 SMD/ 0 THT)
Number of PCBs:,1
Total Components:,19

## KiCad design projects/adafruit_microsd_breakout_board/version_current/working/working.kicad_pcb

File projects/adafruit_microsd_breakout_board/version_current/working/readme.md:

# OOMP Project  
## MicroSD-breakout-board  by adafruit  
  
oomp key: oomp_projects_flat_adafruit_microsd_breakout_board  
(snippet of original readme)  
  
-- Adafruit MicroSD breakout board PCB  
<a href="http://www.adafruit.com/products/254"><br/>  
Click here to purchase one from the Adafruit shop</a>  
  
Not just a simple breakout board, this microSD adapter goes the extra mile - designed for ease of use.  
  
- Onboard 5v->3v regulator provides 150mA for power-hungry cards  
- 3v level shifting means you can use this with ease on either 3v or 5v systems  
- Uses a proper level shifting chip, not resistors: less problems, and faster read/write access  
- Use 3 or 4 digital pins to read and write 2Gb+ of storage!  
- Activity LED lights up when the SD card is being read or written  
- Four -2 mounting holes  
- Push-push socket with card slightly over the edge of the PCB so its easy to insert and remove  
- Comes with 0.1" header (unattached) so you can get it on a breadboard or use wires - your choice  
- Tested and assembled here at the Adafruit factory  
- Works great with Arduino, with tons of example code and wiring diagrams  
  
This repo contains the PCB files for the Adafruit SPI Micro SD (transflash) breakout board  
  
--- License  
  
Adafruit invests time and resources providing this open source design, please support Adafruit and open-source hardware by purchasing products from [Adafruit](https://www.adafruit.com)!  
  
All text above must be included in any redistribution  
  
Designed by Limor Fried/Ladyada for Adafruit Industries.  
Creative Commons Attribution/Share-Alike, all text above must be included in a  
  full source readme at [readme_src.md](readme_src.md)  
  
source repo at: [https://github.com/adafruit/MicroSD-breakout-board](https://github.com/adafruit/MicroSD-breakout-board)  
## Board  

## Schematic  

[schematic pdf](working_schematic.pdf)  
## Images

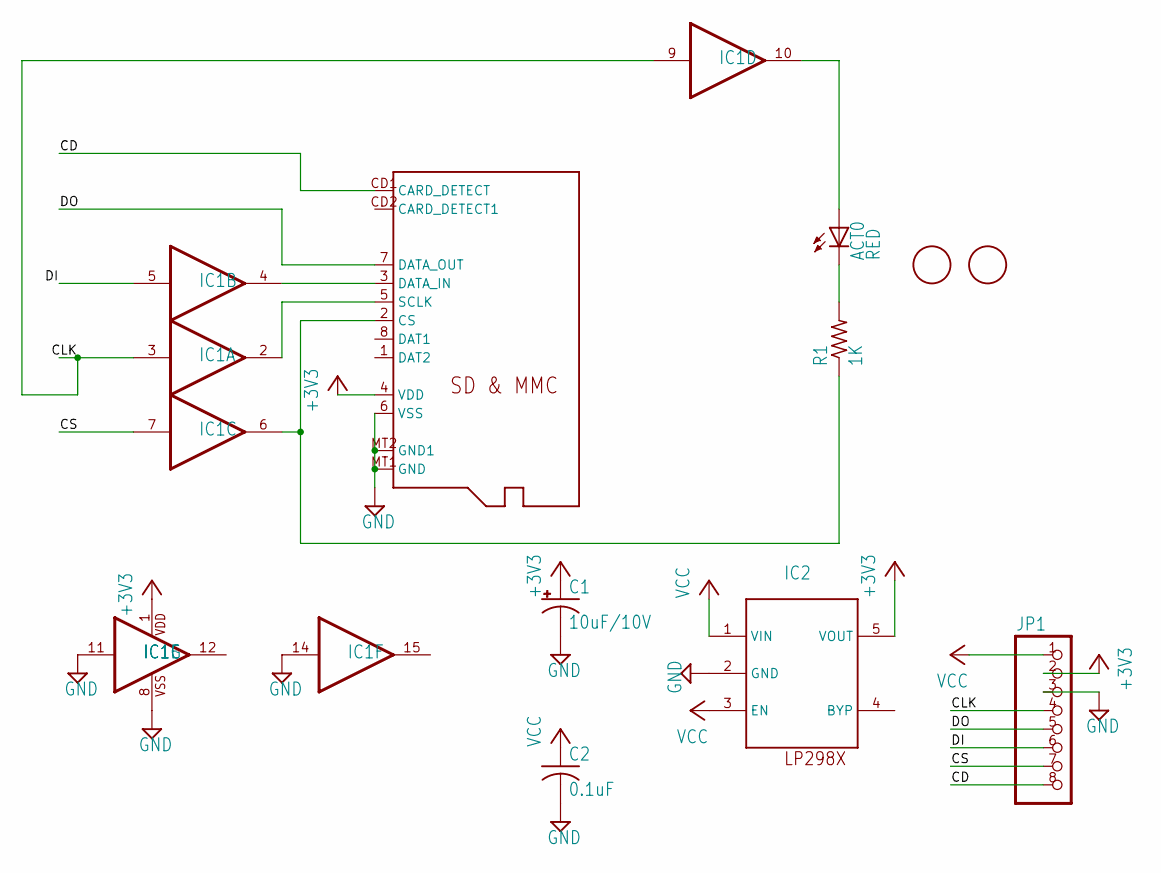
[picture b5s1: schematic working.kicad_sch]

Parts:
ACT0: RED; CHIP-LED0805
C1: 10uF/10V; A_3216-18R
C2: 0.1uF; C0805K
IC1: 4050D; SO16
IC2: LP298XS; SOT23-5L
JP1: PINHD-1X8BIG; 1X08-BIG
R1: 1K; R0805
U$1, U$2: FIDUCIAL; FIDUCIAL_1MM
X1: MICROSD

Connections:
+3V3: C1.+, IC1.1 (VDD), IC2.5 (VOUT), JP1.2, X1.4 (VDD)
CD: JP1.8, X1.CD1 (CARD_DETECT)
CLK: IC1.3 (I), IC1.9 (I), JP1.4
CS: IC1.7 (I), JP1.7
DI: IC1.5 (I), JP1.6
DO: JP1.5, X1.7 (DATA_OUT)
GND: C1.-, C2.2, IC1.8 (VSS), IC1.11 (I), IC1.14 (I), IC2.2 (GND), JP1.3, X1.6 (VSS), X1.MT1 (GND), X1.MT2 (GND1)
unnamed: ACT0.A, IC1.10 (O)
unnamed: IC1.2 (O), X1.5 (SCLK)
unnamed: IC1.6 (O), R1.1, X1.2 (CS)
unnamed: ACT0.C, R1.2
unnamed: IC1.4 (O), X1.3 (DATA_IN)
VCC: C2.1, IC2.1 (VIN), IC2.3 (EN), JP1.1

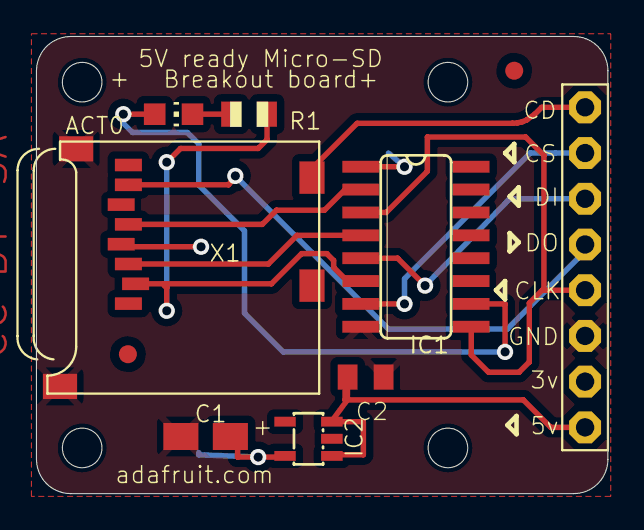
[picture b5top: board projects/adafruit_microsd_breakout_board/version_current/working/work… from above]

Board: 16 copper layers, 31.8 x 25.4 mm, 14 parts (0 on the bottom side), 13 nets.

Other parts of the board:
@HOLE0, @HOLE1, @HOLE2, @HOLE3: (no value)

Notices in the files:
projects/adafruit_ds1307_breakout_board/version_current/working/working.kicad_pcb:
CC BY-SA
